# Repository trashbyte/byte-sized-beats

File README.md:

# byte-sized beats

hardware files and such for modules

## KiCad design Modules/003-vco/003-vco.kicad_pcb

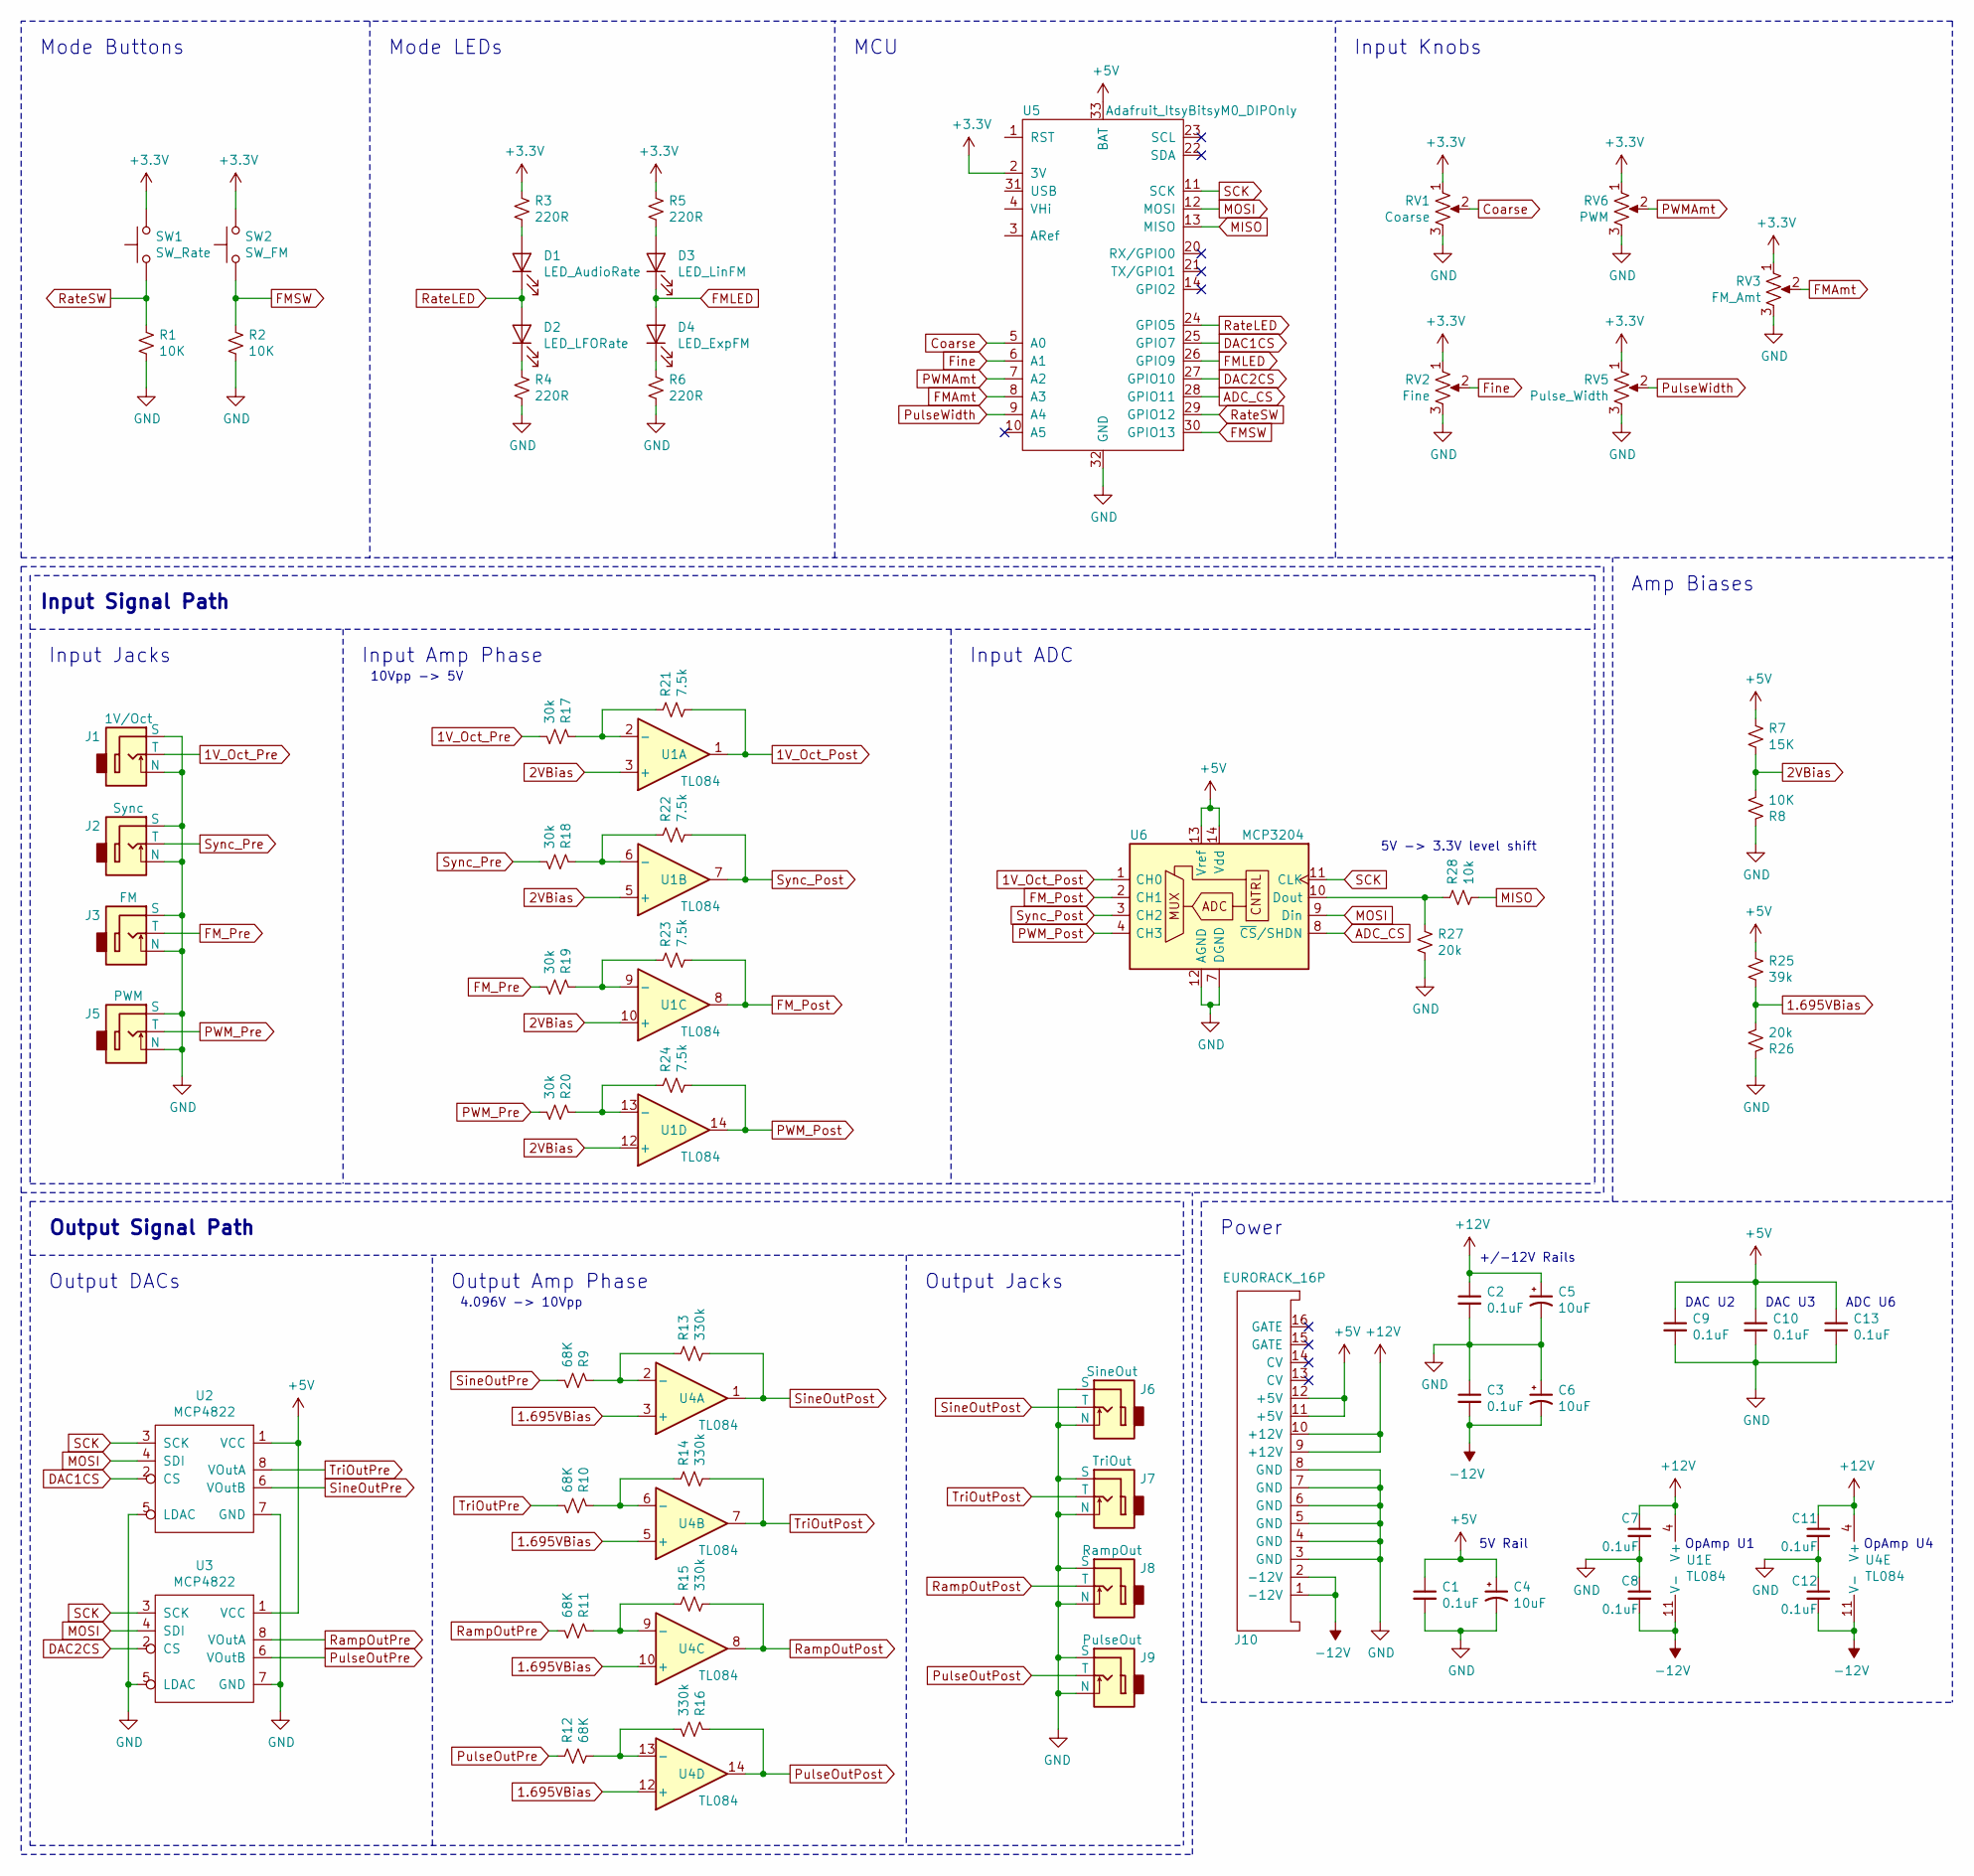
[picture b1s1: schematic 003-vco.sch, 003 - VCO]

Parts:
C1, C2, C3, C7, C8, C9, C10, C11, C12, C13: 0.1uF; C_Disc_D5.0mm_W2.5mm_P5.00mm
C4, C5, C6: 10uF; CP_Radial_D5.0mm_P2.50mm
D1: LED_AudioRate; LED_D3.0mm_Raised
D2: LED_LFORate; LED_D3.0mm_Raised
D3: LED_LinFM; LED_D3.0mm_Raised
D4: LED_ExpFM; LED_D3.0mm_Raised
J1: 1V/Oct; ThonkiconnJack
J2: Sync; ThonkiconnJack
J3: FM; ThonkiconnJack
J5: PWM; ThonkiconnJack
J6: SineOut; ThonkiconnJack
J7: TriOut; ThonkiconnJack
J8: RampOut; ThonkiconnJack
J9: PulseOut; ThonkiconnJack
J10: EURORACK_16P
R1, R2, R8: 10K; R_Axial_DIN0207_L6.3mm_D2.5mm_P2.54mm_Vertical
R3, R4, R5, R6: 220R; R_Axial_DIN0207_L6.3mm_D2.5mm_P2.54mm_Vertical
R7: 15K; R_Axial_DIN0207_L6.3mm_D2.5mm_P2.54mm_Vertical
R9, R10, R11, R12: 68K; R_Axial_DIN0207_L6.3mm_D2.5mm_P2.54mm_Vertical
R13, R14, R15, R16: 330k; R_Axial_DIN0207_L6.3mm_D2.5mm_P2.54mm_Vertical
R17, R18, R19, R20: 30k; R_Axial_DIN0207_L6.3mm_D2.5mm_P2.54mm_Vertical
R21, R22, R23, R24: 7.5k; R_Axial_DIN0207_L6.3mm_D2.5mm_P2.54mm_Vertical
R25: 39k; R_Axial_DIN0207_L6.3mm_D2.5mm_P2.54mm_Vertical
R26, R27: 20k; R_Axial_DIN0207_L6.3mm_D2.5mm_P2.54mm_Vertical
R28: 10k; R_Axial_DIN0207_L6.3mm_D2.5mm_P2.54mm_Vertical
RV1: Coarse; Potentiometer_Bourns_PTV09A-4020U
RV2: Fine; Potentiometer_Bourns_PTV09A-4020U
RV3: FM_Amt; Potentiometer_Bourns_PTV09A-4020U
RV5: Pulse_Width; Potentiometer_Bourns_PTV09A-4020U
RV6: PWM; Potentiometer_Bourns_PTV09A-4020U
SW1: SW_Rate; PushButton_6mm_16mmHeight
SW2: SW_FM; PushButton_6mm_16mmHeight
U1, U4: TL084; DIP-14_W7.62mm
U2, U3: MCP4822; DIP-8_W7.62mm
U5: Adafruit_ItsyBitsyM0_DIPOnly
U6: MCP3204; DIP-14_W7.62mm

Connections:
1.695VBias: R25.2, R26.2, U4.3 (+), U4.5 (+), U4.10 (+), U4.12 (+)
1V_Oct_Post: R21.2, U1.1, U6.1 (CH0)
1V_Oct_Pre: J1.3 (T), R17.2
2VBias: R7.2, R8.2, U1.3 (+), U1.5 (+), U1.10 (+), U1.12 (+)
+3V3: R3.1, R5.1, RV1.1, RV2.1, RV3.1, RV5.1, RV6.1, SW1.2, SW2.2, U5.2 (3V)
+5V: C1.1, C4.1, C9.1, C10.1, C13.1, J10.11 (+5V), J10.12 (+5V), R7.1, R25.1, U2.1 (VCC), U3.1 (VCC), U5.33 (BAT), U6.13 (Vref), U6.14 (Vdd)
+12V: C2.1, C5.1, C7.1, C11.1, J10.9 (+12V), J10.10 (+12V), U1.4 (V+), U4.4 (V+)
-12V: C3.2, C6.2, C8.2, C12.2, J10.1 (-12V), J10.2 (-12V), U1.11 (V-), U4.11 (V-)
ADC_CS: U5.28 (GPIO11), U6.8 (~CS~/SHDN)
Coarse: RV1.2, U5.5 (A0)
DAC1CS: U2.2 (CS), U5.25 (GPIO7)
DAC2CS: U3.2 (CS), U5.27 (GPIO10)
FMAmt: RV3.2, U5.8 (A3)
FMLED: D3.1 (K), D4.2 (A), U5.26 (GPIO9)
FMSW: R2.1, SW2.1, U5.30 (GPIO13)
FM_Post: R23.2, U1.8, U6.2 (CH1)
FM_Pre: J3.3 (T), R19.2
Fine: RV2.2, U5.6 (A1)
GND: C1.2, C2.2, C3.1, C4.2, C5.2, C6.1, C7.2, C8.1, C9.2, C10.2, C11.2, C12.1, C13.2, J1.1 (S), J1.2 (N), J2.1 (S), J2.2 (N), J3.1 (S), J3.2 (N), J5.1 (S), J5.2 (N), J6.1 (S), J6.2 (N), J7.1 (S), J7.2 (N), J8.1 (S), J8.2 (N), J9.1 (S), J9.2 (N), J10.3 (GND), J10.4 (GND), J10.5 (GND), J10.6 (GND), J10.7 (GND), J10.8 (GND), R1.2, R2.2, R4.2, R6.2, R8.1, R26.1, R27.2, RV1.3, RV2.3, RV3.3, RV5.3, RV6.3, U2.5 (LDAC), U2.7 (GND), U3.5 (LDAC), U3.7 (GND), U5.32 (GND), U6.7 (DGND), U6.12 (AGND)
MISO: R28.2, U5.13 (MISO)
MOSI: U2.4 (SDI), U3.4 (SDI), U5.12 (MOSI), U6.9 (Din)
unnamed: D1.2 (A), R3.2
unnamed: D2.1 (K), R4.1
unnamed: D3.2 (A), R5.2
unnamed: D4.1 (K), R6.1
unnamed: R10.1, R14.1, U4.6 (-)
unnamed: R11.1, R15.1, U4.9 (-)
unnamed: R12.2, R16.2, U4.13 (-)
unnamed: R9.1, R13.1, U4.2 (-)
unnamed: R17.1, R21.1, U1.2 (-)
unnamed: R18.1, R22.1, U1.6 (-)
unnamed: R19.1, R23.1, U1.9 (-)
unnamed: R20.1, R24.1, U1.13 (-)
unnamed: R27.1, R28.1, U6.10 (Dout)
PWMAmt: RV6.2, U5.7 (A2)
PWM_Post: R24.2, U1.14, U6.4 (CH3)
PWM_Pre: J5.3 (T), R20.2
PulseOutPost: J9.3 (T), R16.1, U4.14
PulseOutPre: R12.1, U3.6 (VOutB)
PulseWidth: RV5.2, U5.9 (A4)
RampOutPost: J8.3 (T), R15.2, U4.8
RampOutPre: R11.2, U3.8 (VOutA)
RateLED: D1.1 (K), D2.2 (A), U5.24 (GPIO5)
RateSW: R1.1, SW1.1, U5.29 (GPIO12)
SCK: U2.3 (SCK), U3.3 (SCK), U5.11 (SCK), U6.11 (CLK)
SineOutPost: J6.3 (T), R13.2, U4.1
SineOutPre: R9.2, U2.6 (VOutB)
Sync_Post: R22.2, U1.7, U6.3 (CH2)
Sync_Pre: J2.3 (T), R18.2
TriOutPost: J7.3 (T), R14.2, U4.7
TriOutPre: R10.2, U2.8 (VOutA)

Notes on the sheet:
10Vpp -> 5V
5V -> 3.3V level shift
Input Jacks
Input Amp Phase
Input ADC
Output Jacks
Output DACs
Output Amp Phase
4.096V -> 10Vpp
Mode Buttons
Mode LEDs
MCU
Input Knobs
Power
Amp Biases
Output Signal Path
Input Signal Path
DAC U2
DAC U3
ADC U6
OpAmp U1
OpAmp U4
+/-12V Rails
5V Rail

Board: 2 copper layers, 67 parts (43 on the bottom side), 51 nets, no tracks yet.

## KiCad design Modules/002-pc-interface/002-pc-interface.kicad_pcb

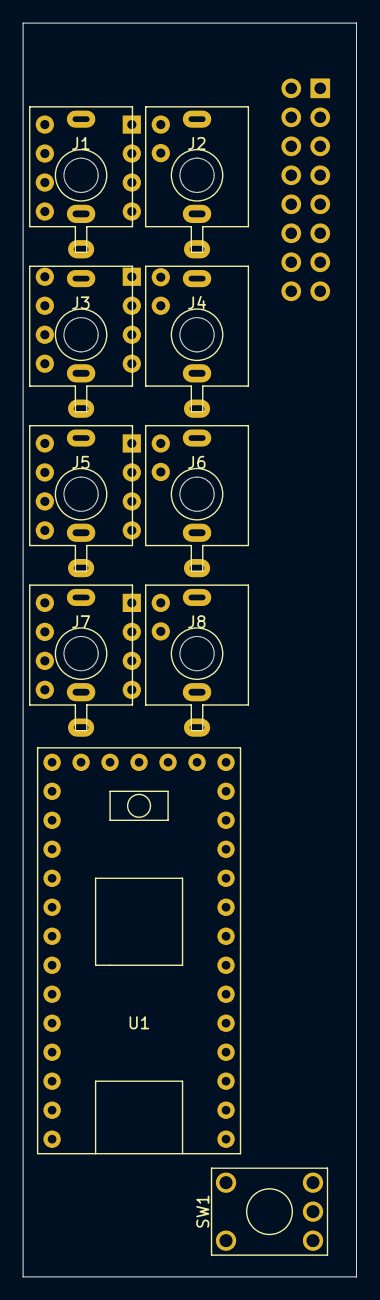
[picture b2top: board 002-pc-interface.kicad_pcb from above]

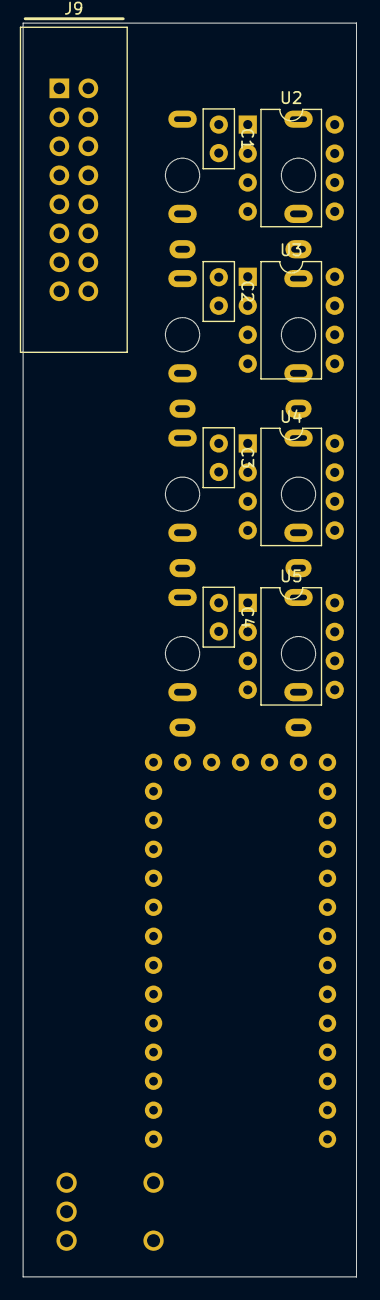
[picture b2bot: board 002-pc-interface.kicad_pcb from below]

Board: 2 copper layers, 29.2 x 109.9 mm, 19 parts (9 on the bottom side), 19 nets, no tracks yet.

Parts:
C1, C2, C3, C4: 0.1uF; C_Disc_D5.0mm_W2.5mm_P2.50mm
J1, J2, J3, J4, J5, J6, J7, J8: ThonkiconnJack
J9: EURORACK_16P
SW1: SW_SPST; KSA_Tactile_SPST
U1: Adafruit_ItsyBitsyM0
U2, U3, U4, U5: MCP4822; DIP-8_W7.62mm

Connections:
+5V: C1.1, C2.1, C3.1, C4.1, J9.11, J9.12, U1.33, U2.1, U3.1, U4.1, U5.1
+12V: J9.9, J9.10
-12V: J9.1, J9.2
CS_DAC1: U1.21, U2.2
CS_DAC2: U1.14, U3.2
CS_DAC3: U1.18, U4.2
CS_DAC4: U1.19, U5.2
GND: C1.2, C2.2, C3.2, C4.2, J1.1, J2.1, J3.1, J4.1, J5.1, J6.1, J7.1, J8.1, J9.3, J9.4, J9.5, J9.6, J9.7, J9.8, SW1.1, U1.32, U2.5, U2.7, U3.5, U3.7, U4.5, U4.7, U5.5, U5.7
MOSI: U1.12, U2.4, U3.4, U4.4, U5.4
unnamed: J1.3, U2.8
unnamed: J2.3, U2.6
unnamed: J3.3, U3.8
unnamed: J4.3, U3.6
unnamed: J5.3, U4.8
unnamed: J6.3, U4.6
unnamed: J7.3, U5.8
unnamed: J8.3, U5.6
unnamed: SW1.2, U1.1
SCK: U1.11, U2.3, U3.3, U4.3, U5.3

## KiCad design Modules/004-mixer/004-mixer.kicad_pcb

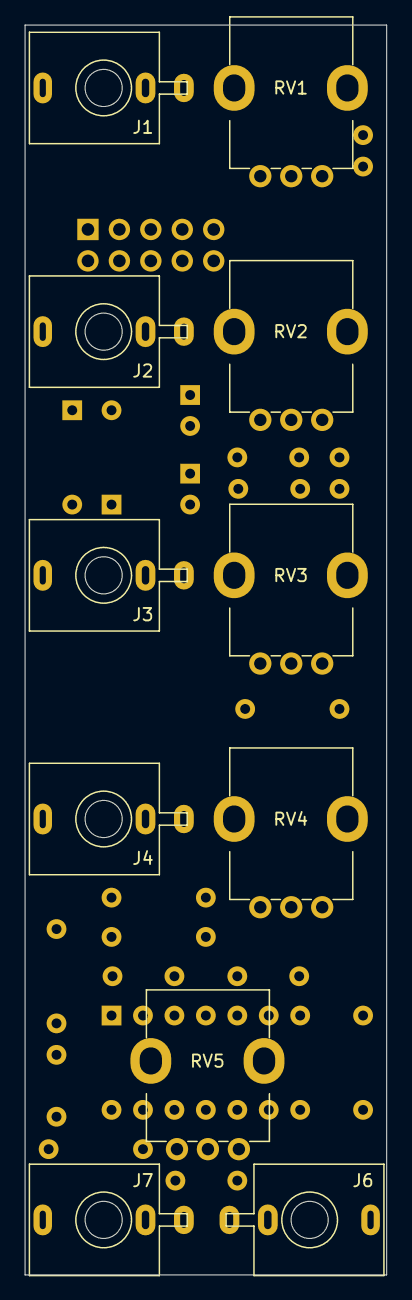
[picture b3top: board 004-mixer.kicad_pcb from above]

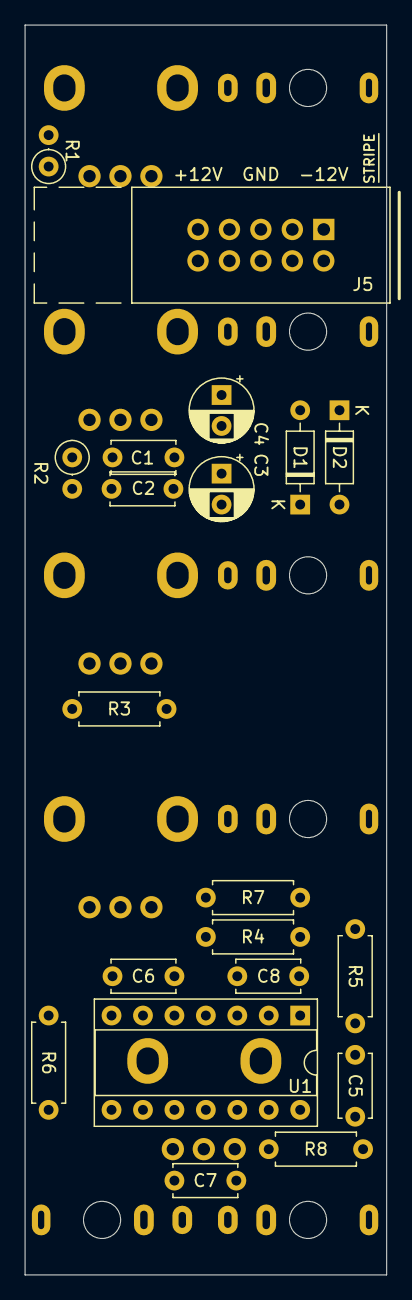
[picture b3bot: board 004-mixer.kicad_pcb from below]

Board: 2 copper layers, 29.2 x 101.0 mm, 36 parts (20 on the bottom side), 21 nets, no tracks yet.

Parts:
C1, C2, C6, C7: 0.1uF; C_Disc_D5.0mm_W2.5mm_P5.00mm
C3, C4: 10uF; CP_Radial_D5.0mm_P2.50mm
C5, C8: 47pF; C_Disc_D5.0mm_W2.5mm_P5.00mm
D1, D2: D; D_DO-35_SOD27_P7.62mm_Horizontal
J1, J2, J3, J4, J6, J7: ThonkiconnJack
J5: EURORACK_10P
K1, K2, K3, K4, K5: Knob_11mm
R1, R2: 50K; R_Axial_DIN0207_L6.3mm_D2.5mm_P2.54mm_Vertical
R3, R4, R5, R7: 50K; R_Axial_DIN0207_L6.3mm_D2.5mm_P7.62mm_Horizontal
R6, R8: 1K; R_Axial_DIN0207_L6.3mm_D2.5mm_P7.62mm_Horizontal
RV1, RV2, RV3, RV4, RV5: A50K; Potentiometer_Bourns_PTV09A-4020U
U1: TL084; DIP-14_W7.62mm_Socket

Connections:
+12V: C1.2, C3.1, C6.2, D1.1, U1.4
-12V: C2.1, C4.2, C7.1, D2.2, U1.11
GND: C1.1, C2.2, C3.2, C4.1, C6.1, C7.2, J1.1, J1.2, J2.1, J2.2, J3.1, J3.2, J4.1, J4.2, J5.3, J5.4, J5.5, J5.6, J5.7, J5.8, J6.1, J6.2, J7.1, J7.2, RV1.3, RV2.3, RV3.3, RV4.3, U1.3, U1.5, U1.10, U1.12
unnamed: C5.1, R5.2, R8.2, RV5.3, U1.1
unnamed: C5.2, R1.1, R2.1, R3.1, R4.1, RV5.2, U1.2
unnamed: C8.1, R6.2, R7.1, U1.7
unnamed: C8.2, R5.1, R7.2, U1.6
unnamed: D1.2, J5.9, J5.10
unnamed: D2.1, J5.1, J5.2
unnamed: J1.3, RV2.1
unnamed: J2.3, RV3.1
unnamed: J3.3, RV4.1
unnamed: J4.3, RV1.1
unnamed: J6.3, R6.1
unnamed: J7.3, R8.1
unnamed: R1.2, RV1.2
unnamed: R2.2, RV2.2
unnamed: R3.2, RV3.2
unnamed: R4.2, RV4.2
unnamed: U1.8, U1.9
unnamed: U1.13, U1.14

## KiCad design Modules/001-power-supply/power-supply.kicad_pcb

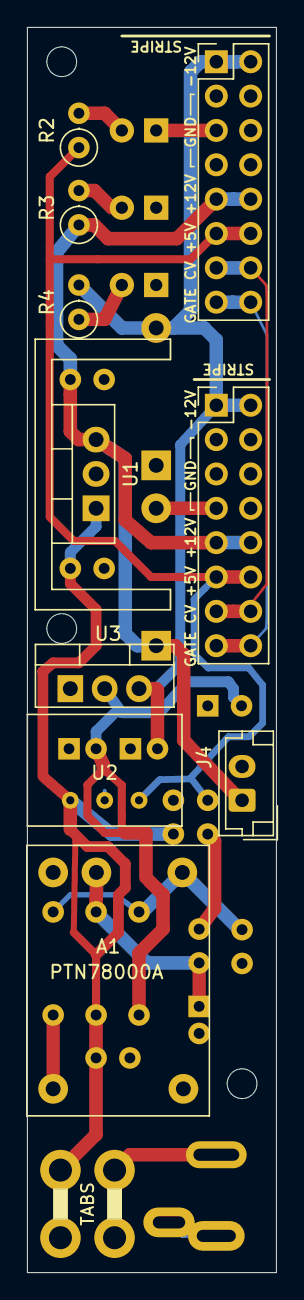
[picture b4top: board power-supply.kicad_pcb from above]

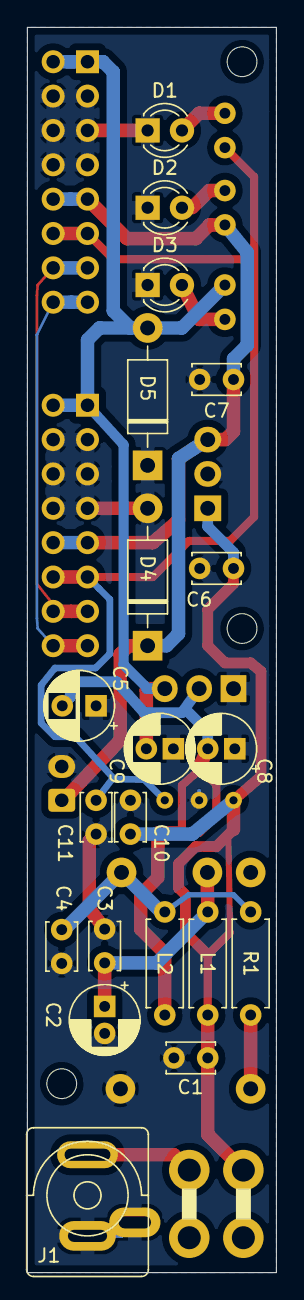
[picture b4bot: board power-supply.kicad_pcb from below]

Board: 2 copper layers, 18.4 x 92.1 mm, 34 parts (20 on the bottom side), 15 nets.

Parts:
A1: PTN78000A
C1, C4: 4.7uF; C_Disc_D3.4mm_W2.1mm_P2.50mm
C2, C8, C9: 100uF; CP_Radial_D5.0mm_P2.00mm
C3, C10, C11: 10uF; C_Disc_D3.4mm_W2.1mm_P2.50mm
C5: 100uF; CP_Radial_D5.0mm_P2.50mm
C6: 0.33uF; C_Disc_D3.4mm_W2.1mm_P2.50mm
C7: 0.1uF; C_Disc_D3.4mm_W2.1mm_P2.50mm
D1, D2, D3: LED; LED_D3.0mm_Raised
D4, D5: 1N4001; D_DO-41_SOD81_P10.16mm_Horizontal
H1, H2, H3: MountingHole_M2
J1: Barrel_Jack_Switch; BARREL_JACK_VERTICAL_MERGED
J2, J3: EURORACK_16P; PinHeader_2x08_P2.54mm_Vertical
J4: Conn_01x02; JST_EH_B2B-EH-A_1x02_P2.50mm_Vertical
L1, L2: 1-5uH; R_Axial_DIN0207_L6.3mm_D2.5mm_P7.62mm_Horizontal
R1: 100R 1%; R_Axial_DIN0207_L6.3mm_D2.5mm_P7.62mm_Horizontal
R2: 330R; R_Axial_DIN0207_L6.3mm_D2.5mm_P2.54mm_Vertical
R3, R4: 1k; R_Axial_DIN0207_L6.3mm_D2.5mm_P2.54mm_Vertical
SW1: SW_SPST; DUAL_TAB_4.8MM
U1: L7812; TO-220-3_Vertical_Heatsink
U2: R-78E5.0; R-78EXX
U3: L7912; TO-220-3_Vertical

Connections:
+5V: C11.1, J2.11, J2.12, J3.11, J3.12, R2.1, U2.3
+12V: C7.1, D4.1, J2.9, J2.10, J3.9, J3.10, J4.1, R3.1, U1.3
+15V: C1.1, C6.1, C10.1, L1.1, SW1.2, U1.1, U2.1
-12V: C9.2, D5.2, J2.1, J2.2, J3.1, J3.2, R4.2, U3.3
-15V: C5.2, C8.2, L2.2, U3.2
/CV: J2.13, J2.14, J3.13, J3.14
/GATE: J2.15, J2.16, J3.15, J3.16
GND: A1.5, C1.2, C2.2, C3.2, C4.2, C5.1, C6.2, C7.2, C8.1, C9.1, C10.2, C11.2, D1.1, D2.1, D3.1, D4.2, D5.1, J1.2, J1.3, J2.3, J2.4, J2.5, J2.6, J2.7, J2.8, J3.3, J3.4, J3.5, J3.6, J3.7, J3.8, J4.2, U1.2, U2.2, U3.1
unnamed: A1.1, C4.1, L2.1, R1.2
unnamed: A1.2, C2.1, C3.1, L1.2
unnamed: A1.4, R1.1
unnamed: D1.2, R2.2
unnamed: D2.2, R3.2
unnamed: D3.2, R4.1
unnamed: J1.1, SW1.1

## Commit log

2020-03-10 initial commit ([001] power supply)
2020-03-10 reorganized
2020-03-10 cleaned up after reorganizing
2020-03-10 added readme, license, [001] model
2020-03-24 added [002] pc interface module (WIP), [003] vco module (WIP), [004] mixer module
